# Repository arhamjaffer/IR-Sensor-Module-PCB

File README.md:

# IR-Sensor-Module-PCB
Custom IR Sensor Module PCB designed in KiCad for object detection and embedded system applications.
# 🔴 IR Sensor Module PCB

<div align="center">

</div>

---

## 📌 Overview

This project presents a custom-designed Infrared (IR) Sensor Module PCB developed using KiCad. The module is intended for object detection and proximity sensing applications in embedded systems, robotics, and automation projects.

The PCB was designed with a focus on compact layout, reliable signal routing, and ease of manufacturing.

---

## ✨ Features

- Infrared object detection
- Compact PCB footprint
- Easy integration with microcontrollers
- Suitable for robotics projects
- Low-cost and manufacturable design
- Custom schematic and PCB layout

---

## 🛠️ Design Tools

| Tool | Purpose |
|--------|---------|
| KiCad | Schematic Design |
| KiCad PCB Editor | PCB Layout |
| KiCad 3D Viewer | 3D Visualization |

---

## 📷 Project Images

<h2 align="center">📷 Project Gallery</h2>

<h3 align="center">Circuit Schematic</h3>

<h3 align="center">PCB Layout</h3>

<h3 align="center">3D PCB Views</h3>

<table align="center">
<tr>
<td align="center">
<br>
<b>Front View</b>
</td>

<td align="center">
<br>
<b>Back View</b>
</td>
</tr>
</table>

---
## 🎯 Applications

- Obstacle Detection
- Line Following Robots
- Automation Systems
- Embedded Projects
- Arduino Projects
- ESP32 Projects

---

## 📈 Skills Demonstrated

✔ Schematic Capture

✔ PCB Layout Design

✔ Component Placement

✔ Signal Routing

✔ Hardware Prototyping

✔ Design for Manufacturing (DFM)

---

## 👨‍💻 Author

### Arham Jaffer

Electrical Engineering Student

PCB Designer | Embedded Systems Developer | IoT Enthusiast

---

⭐ If you found this project useful, consider giving it a star.

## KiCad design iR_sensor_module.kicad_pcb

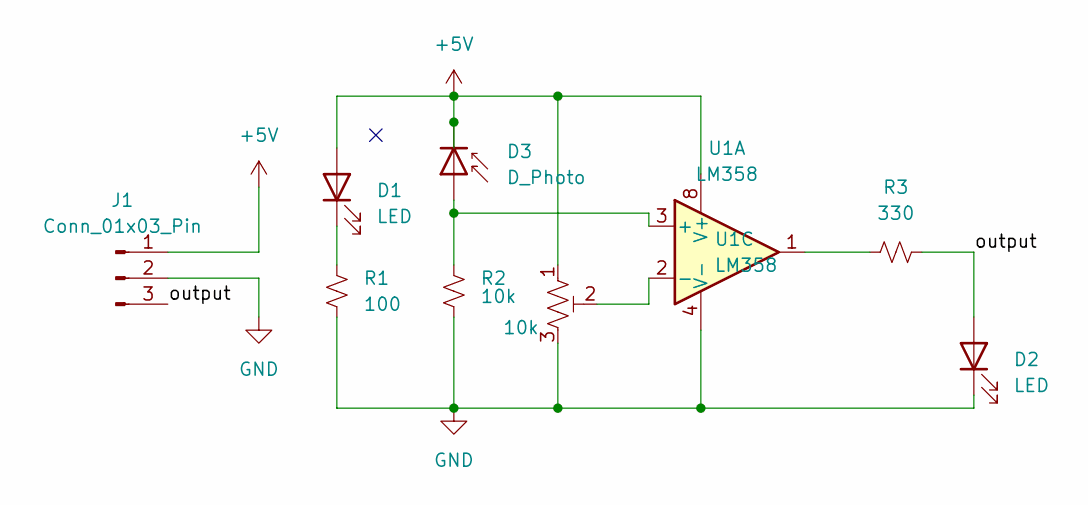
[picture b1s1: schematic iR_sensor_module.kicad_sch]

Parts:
D1: LED; LED_D3.0mm_Horizontal_O1.27mm_Z2.0mm
D2: LED; LED_1206_3216Metric_Pad1.42x1.75mm_HandSolder
D3: D_Photo; LED_D3.0mm_Horizontal_O1.27mm_Z2.0mm
J1: Conn_01x03_Pin; PinHeader_1x03_P2.54mm_Horizontal
R1: 100; R_1206_3216Metric_Pad1.30x1.75mm_HandSolder
R2: 10k; R_1206_3216Metric_Pad1.30x1.75mm_HandSolder
R3: 330; R_1206_3216Metric_Pad1.30x1.75mm_HandSolder
RV1: 10k; Potentiometer_Bourns_3386W_Horizontal
U1: LM358; DIP-8_W7.62mm_SMDSocket_SmallPads

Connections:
+5V: D1.2 (A), D3.1 (K), J1.1, RV1.1, U1.8 (V+)
/output: D2.2 (A), J1.3, R3.2
GND: D2.1 (K), J1.2, R1.2, R2.2, RV1.3, U1.4 (V-)
unnamed: D1.1 (K), R1.1
unnamed: D3.2 (A), R2.1, U1.3 (+)
unnamed: R3.1, U1.1
unnamed: RV1.2, U1.2 (-)

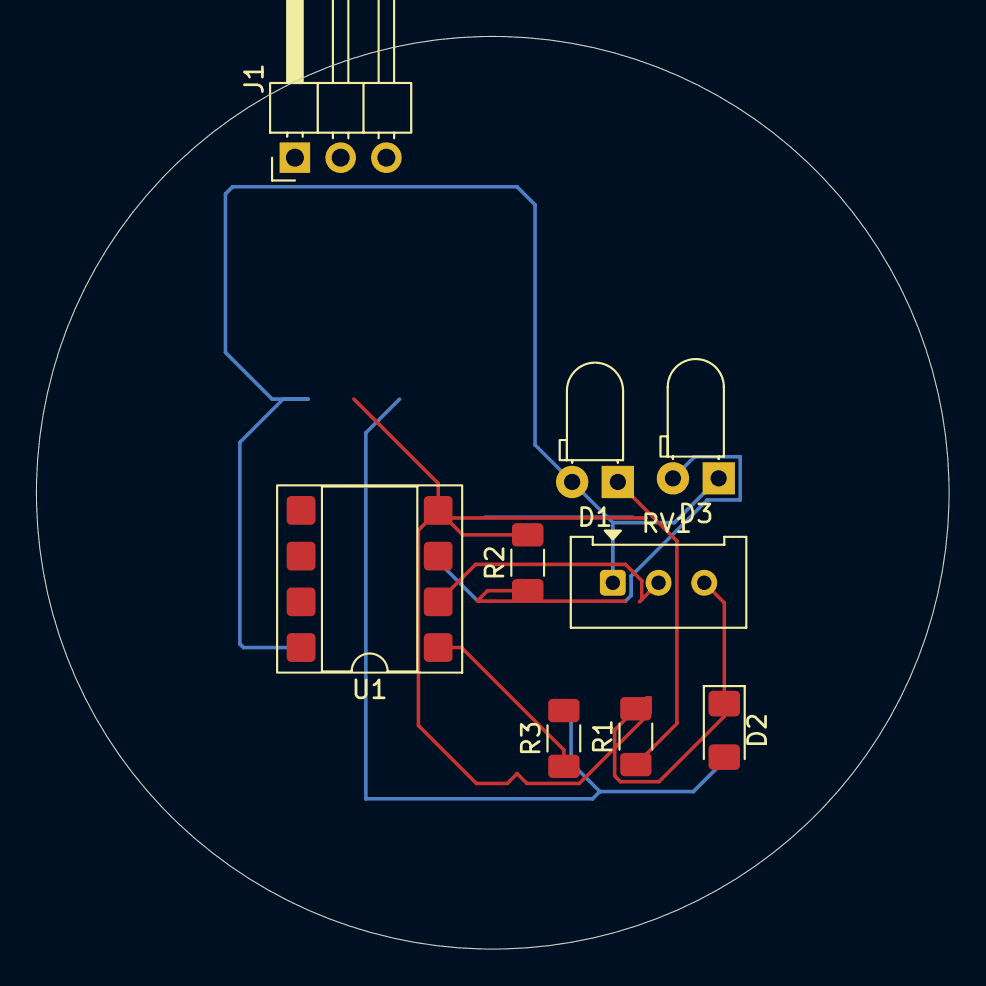
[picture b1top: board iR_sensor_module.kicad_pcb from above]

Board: 2 copper layers, 50.7 x 50.7 mm, 9 parts (0 on the bottom side), 7 nets.
